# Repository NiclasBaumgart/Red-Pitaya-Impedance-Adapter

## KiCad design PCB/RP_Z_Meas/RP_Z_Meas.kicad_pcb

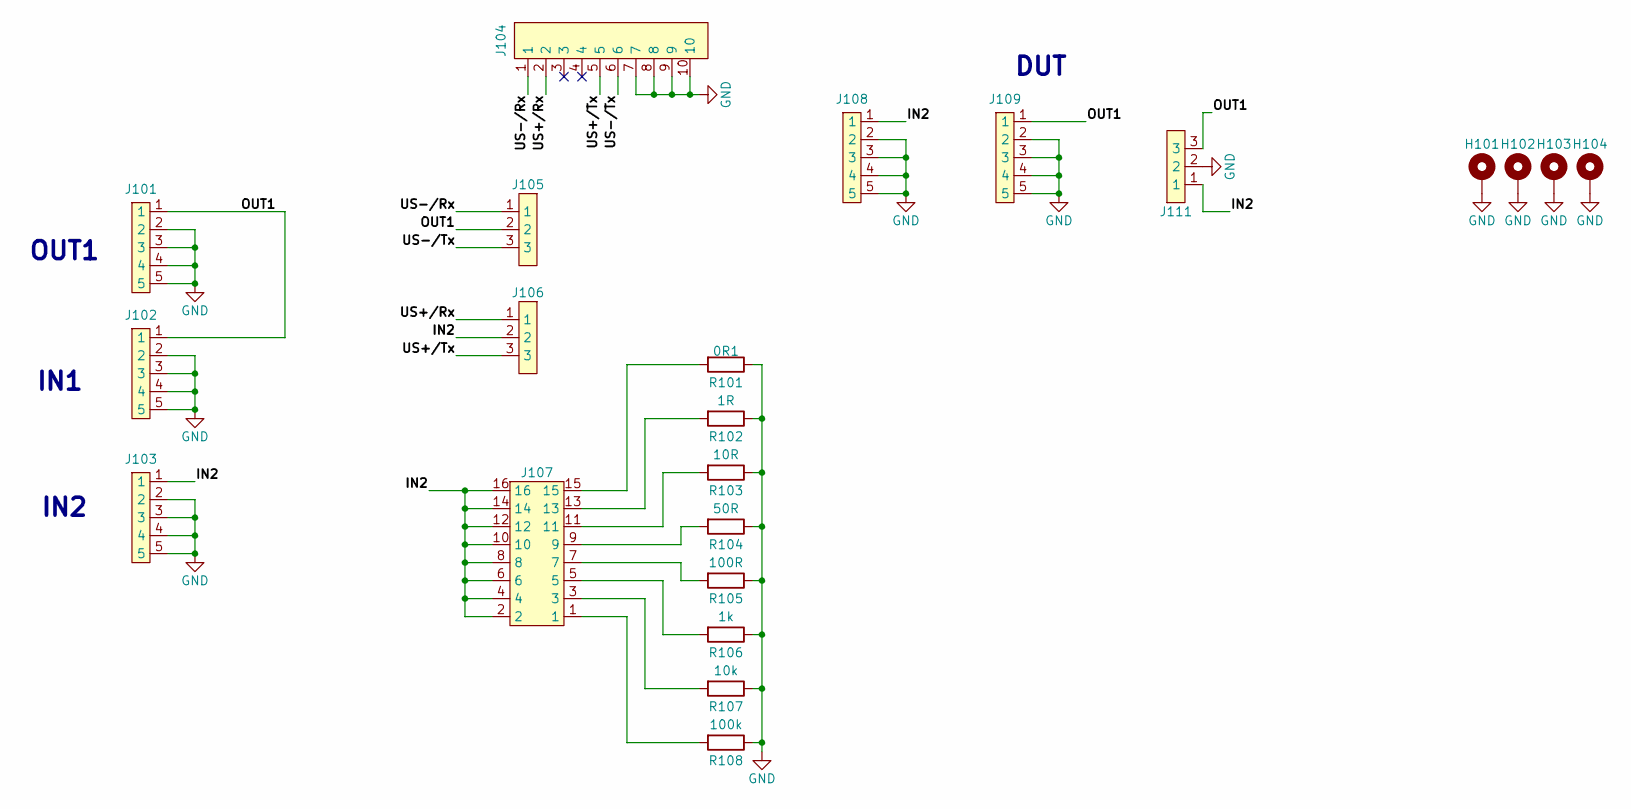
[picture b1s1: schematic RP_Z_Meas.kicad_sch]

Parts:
H101, H102, H103, H104: MountingHole_Pad; MountingHole_3.2mm_M3_Pad_Via
J101, J102, J103, J108, J109: Generic-5P; BNC_Jack_90
J104: Generic-7P; F31K-1A7H1-11006
J105, J106: PinHeader_1x03_P2.54mm_Vertical
J107: PinHeader_2x08_P2.54mm_Vertical
J111: PhoenixContact_MC_1,5_3-G-3.81_1x03_P3.81mm_Horizontal
R101: 0R1; R_0805; Tolerance 1%; Part Number Generic
R102: 1R; R_0805; Tolerance 1%; Part Number Generic
R103: 10R; R_0805; Tolerance 1%; Part Number Generic
R104: 50R; R_0805; Tolerance 1%; Part Number Generic
R105: 100R; R_0805; Tolerance 1%; Part Number Generic
R106: 1k; R_0805; Tolerance 1%; Part Number Generic
R107: 10k; R_0805; Tolerance 1%; Part Number Generic
R108: 100k; R_0805; Tolerance 1%; Part Number Generic

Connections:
/IN2: J103.1, J106.2, J107.2, J107.4, J107.6, J107.8, J107.10, J107.12, J107.14, J107.16, J108.1, J111.1
/OUT1: J101.1, J102.1, J105.2, J109.1, J111.3
/US+/Rx: J104.2, J106.1
/US+/Tx: J104.5, J106.3
/US-/Rx: J104.1, J105.1
/US-/Tx: J104.6, J105.3
GND: H101.1, H102.1, H103.1, H104.1, J101.2, J101.3, J101.4, J101.5, J102.2, J102.3, J102.4, J102.5, J103.2, J103.3, J103.4, J103.5, J104.7, J104.8, J104.9, J104.10, J108.2, J108.3, J108.4, J108.5, J109.2, J109.3, J109.4, J109.5, J111.2, R101.2, R102.2, R103.2, R104.2, R105.2, R106.2, R107.2, R108.2
unnamed: J107.1, R108.1
unnamed: J107.3, R107.1
unnamed: J107.5, R106.1
unnamed: J107.7, R105.1
unnamed: J107.9, R104.1
unnamed: J107.11, R103.1
unnamed: J107.13, R102.1
unnamed: J107.15, R101.1

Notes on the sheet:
IN1
OUT1
IN2
DUT

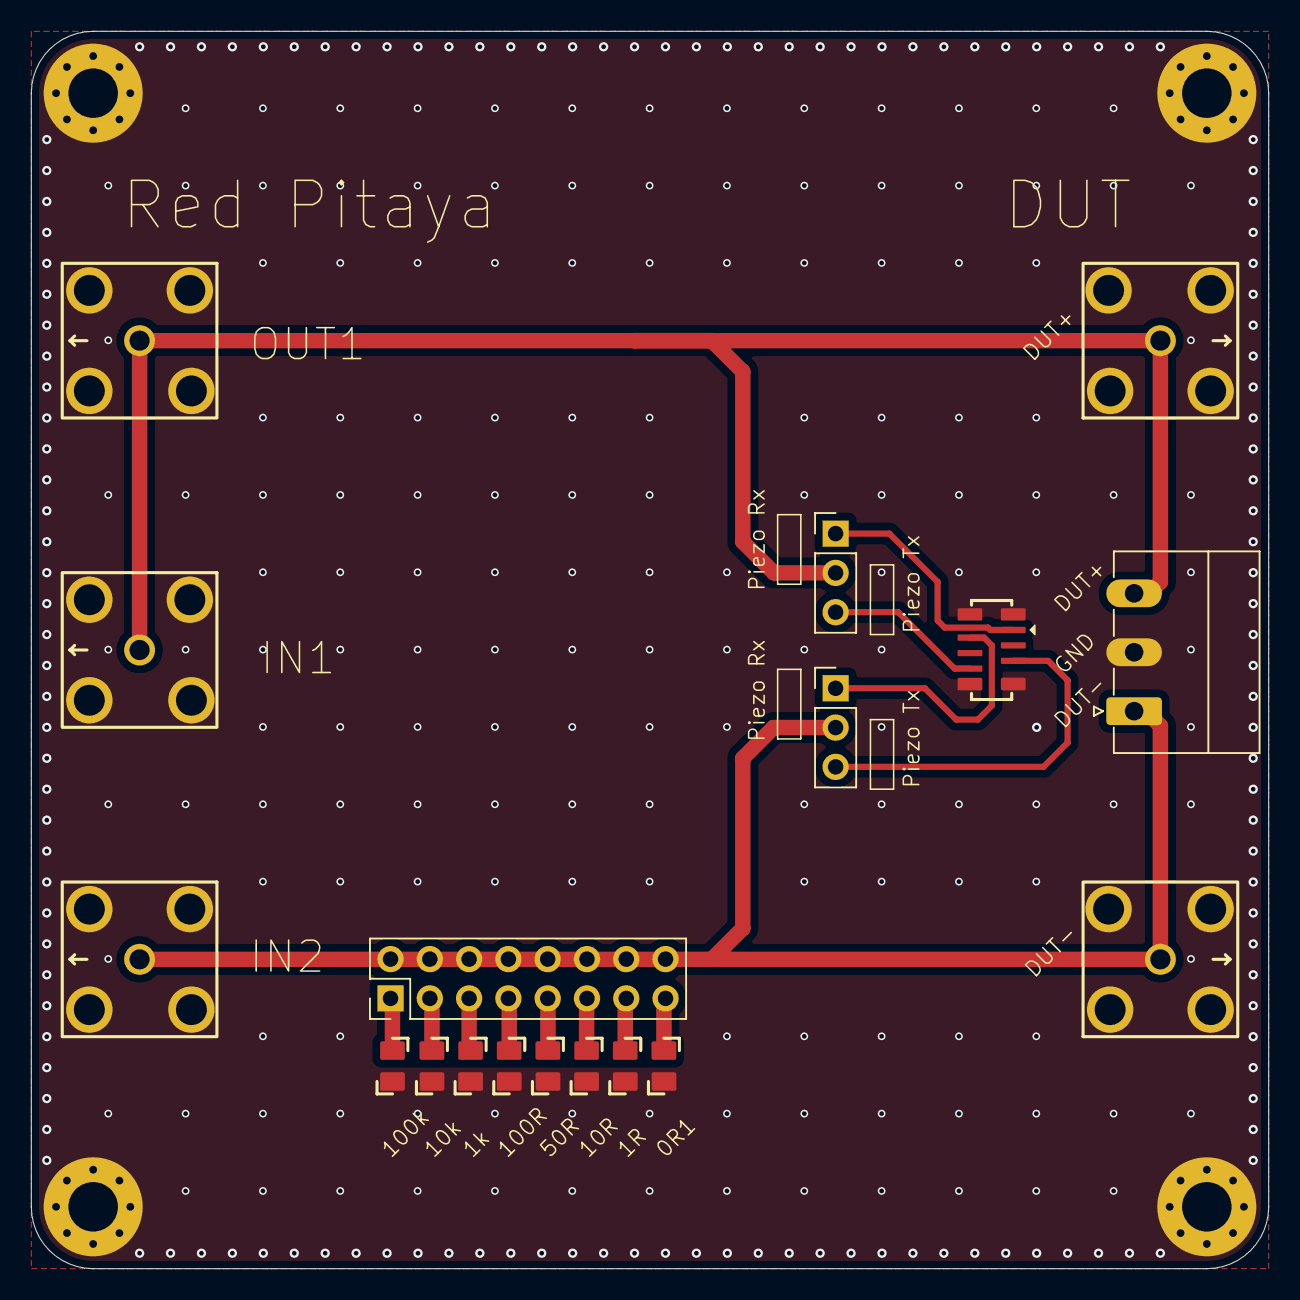
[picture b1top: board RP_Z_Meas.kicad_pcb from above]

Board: 2 copper layers, 80.0 x 80.0 mm, 22 parts (0 on the bottom side), 15 nets.

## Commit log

2024-12-10 created repo
2024-12-10 include newest PCB V1
